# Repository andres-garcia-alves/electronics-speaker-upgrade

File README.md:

# Speaker Upgrade

Speaker modernization (50 watts, 6 ohm) to function as a semi-portable, independent device, separate from the original audio system.

The following features are added:
- Bluetooth audio reception.
- AUX input with a 3.5mm jack for wired connection.
- Slider potentiometer for volume control.
- DC connector for 12V power supply.
- On/off switch button.

&nbsp;

### Notes:

- Power input: 12 VDC
- 2 PCBs are included:
  - Main PCB: for power, BT and audio amplifier features.
  - Auxiliar PCB (for UX): volume slider, LED and AUX audio jack.

&nbsp;

### List of Materials

- 1 x Speaker 10+ watts, 6 ohms
- 1 x Audio Amplifier AN7522N 5W+5W + Heat Sink
- 1 x BT receiver WIN-668 module
- 1 x Lineal Regulator TP7805 + Heat Sink
- 1 x Capacitor 2200uf (electrolitic)
- 1 x Capacitor 1000uf (electrolitic)
- 1 x Capacitor 470uf (electrolitic)
- 1 x Capacitor 10uf (electrolitic)
- 4 x Capacitor 100nf (ceramic)
- 1 x Potentiometer 50K (slider)
- 1 x Resistor 1M ohms
- 1 x Resistor 330K ohms
- 1 x Resistor 47K ohms
- 2 x Resistor 22K ohms
- 2 x Resistor 10K ohms
- 4 x Resistor 3.3K ohms
- 1 x Resistor 680 ohms
- 1 x LED 5mm
- 1 x Audio jack 3.5mm
- 1 x Switch button (audio source)
- 1 x Rocker button (power on/off)
- 1 x DC Jack (power)
- 1 x JST 2-pins connector (or similar)
- 1 x JST 5-pins connector (or similar)
- 1 x JST 6-pins connector (or similar)
- Wires

&nbsp;

### Screenshots

| Breadboard                                           | Assembly                                             |
|------------------------------------------------------|------------------------------------------------------|
|                   |                     |

| Assembly                                             | Assembly                                             |
|------------------------------------------------------|------------------------------------------------------|
|                     |                     |

| Schematics Diagram                                   | PCB Diagram                                          |
|------------------------------------------------------|------------------------------------------------------|
|              |                     |

| PCB Render 3D                                        | PCB Render 3D                                        |
|------------------------------------------------------|------------------------------------------------------|
|               |            |

| Project Final                                        | Project Final                                        |
|------------------------------------------------------|------------------------------------------------------|
|                |                |

See 'Resources' folder for more pictures & videos of the project.

&nbsp;

### Version History

v1.0 (2026.02.15) - Adding base schematics and PCB.  
v1.1 (2026.02.16) - Improvements on schematics and PCB.  
v1.2 (2026.02.17) - Minor improvements on schematics and PCB.  
v1.3 (2026.02.21) - Minor improvements on schematics and PCB.  

&nbsp;

This source code is licensed under GPL v3.0  
Please send me your feedback about this project: andres.garcia.alves@gmail.com

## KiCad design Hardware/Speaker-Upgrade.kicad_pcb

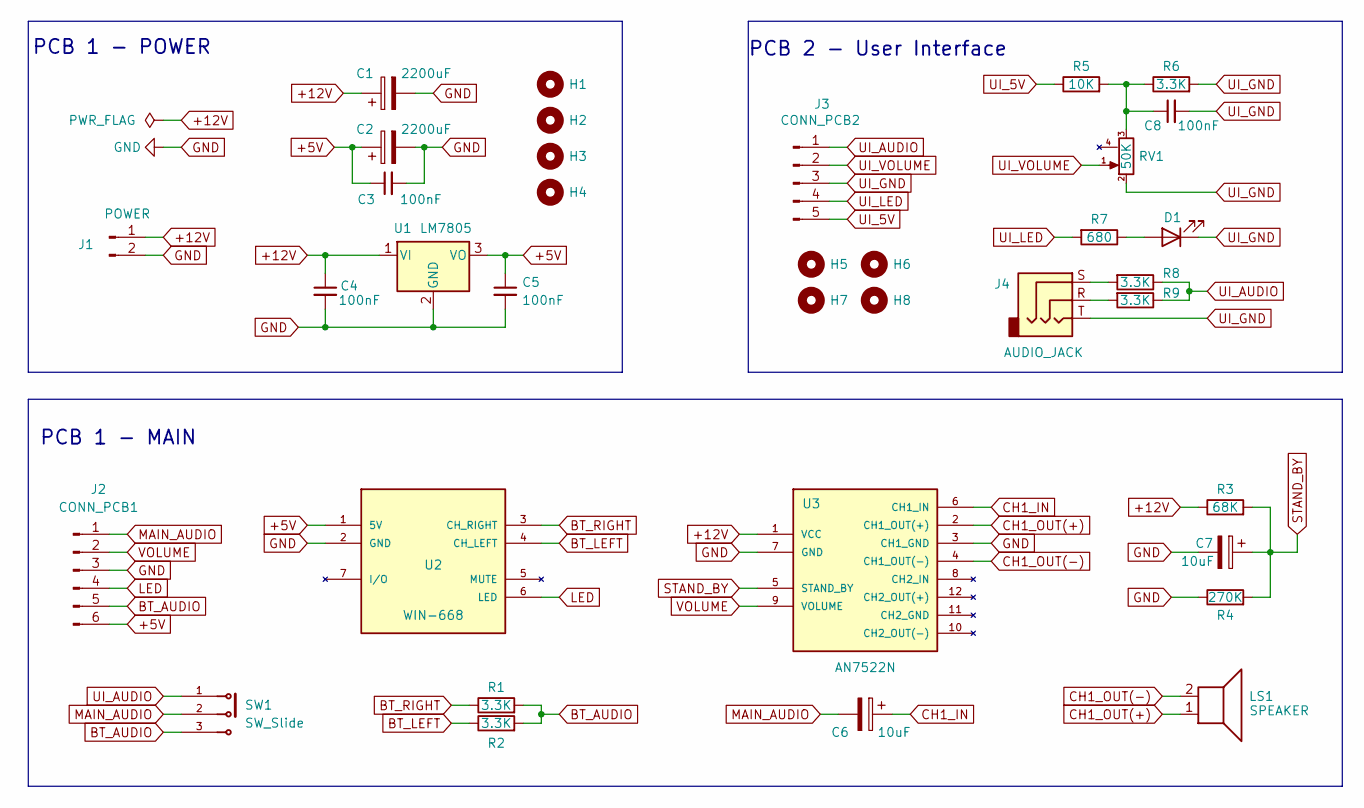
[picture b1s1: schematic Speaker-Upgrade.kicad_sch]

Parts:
C1: 2200uF; C_Radial_D10.0mm_H12.5mm_P5.00mm
C2: 2200uF; C_Radial_D10.0mm_H16.0mm_P5.00mm
C3, C4, C5, C8: 100nF; C_Disc_D6.0mm_W2.5mm_P5.00mm
C6: 10uF; C_Radial_D10.0mm_H16.0mm_P5.00mm
C7: 10uF; C_Radial_D6.3mm_H11.0mm_P2.50mm
D1: LED; LED_D5.0mm
H1, H2, H3, H4, H5, H6, H7, H8: MountingHole; MountingHole_2.2mm_M2
J1: POWER; JST_EH_B2B-EH-A_1x02_P2.50mm_Vertical
J2: CONN_PCB1; PinHeader_2x06_P2.54mm_Vertical
J3: CONN_PCB2; JST_EH_S5B-EH_1x05_P2.50mm_Horizontal
J4: AUDIO_JACK; Jack_3.5mm_Vertical
LS1: SPEAKER; JST_EH_B2B-EH-A_1x02_P2.50mm_Vertical
R1, R2: 3.3K; R_Axial_DIN0207_L6.3mm_D2.5mm_P2.54mm_Vertical
R3: 68K; R_Axial_DIN0207_L6.3mm_D2.5mm_P2.54mm_Vertical
R4: 270K; R_Axial_DIN0207_L6.3mm_D2.5mm_P2.54mm_Vertical
R5: 10K; R_Axial_DIN0207_L6.3mm_D2.5mm_P7.62mm_Horizontal
R6, R8, R9: 3.3K; R_Axial_DIN0207_L6.3mm_D2.5mm_P7.62mm_Horizontal
R7: 680; R_Axial_DIN0207_L6.3mm_D2.5mm_P7.62mm_Horizontal
RV1: 50K; Potentiometer_Custom_Variant_A
SW1: SW_Slide; SW_1825159-1
U1: LM7805; TO-220-3_Vertical
U2: WIN-668; PinSocket_1x07_P2.54mm_Vertical
U3: AN7522N; Audio_Amplifier_AN7522N

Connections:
+5V: C2.1, C3.1, C5.1, J2.6, U1.3 (VO), U2.1 (5V)
+12V: C1.1, C4.1, J1.1, R3.1, U1.1 (VI), U3.1 (VCC)
BT_AUDIO: J2.5, R1.2, R2.2, SW1.3
BT_LEFT: R2.1, U2.4 (CH_LEFT)
BT_RIGHT: R1.1, U2.3 (CH_RIGHT)
CH1_IN: C6.1, U3.6 (CH1_IN)
CH1_OUT(+): LS1.1, U3.2 (CH1_OUT(+))
CH1_OUT(-): LS1.2, U3.4 (CH1_OUT(-))
GND: C1.2, C2.2, C3.2, C4.2, C5.2, C7.2, J1.2, J2.3, R4.1, U1.2 (GND), U2.2 (GND), U3.3 (CH1_GND), U3.7 (GND)
LED: J2.4, U2.6 (LED)
MAIN_AUDIO: C6.2, J2.1, SW1.2
unnamed: C8.1, R5.2, R6.1, RV1.3
unnamed: D1.2 (A), R7.1
unnamed: J4.R, R9.2
unnamed: J4.S, R8.2
STAND_BY: C7.1, R3.2, R4.2, U3.5 (STAND_BY)
UI_5V: J3.5, R5.1
UI_AUDIO: J3.1, R8.1, R9.1, SW1.1
UI_GND: C8.2, D1.1 (K), J3.3, J4.T, R6.2, RV1.2
UI_LED: J3.4, R7.2
UI_VOLUME: J3.2, RV1.1
VOLUME: J2.2, U3.9 (VOLUME)

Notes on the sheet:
PCB 2 - User Interface
PCB 1 - POWER
PCB 1 - MAIN

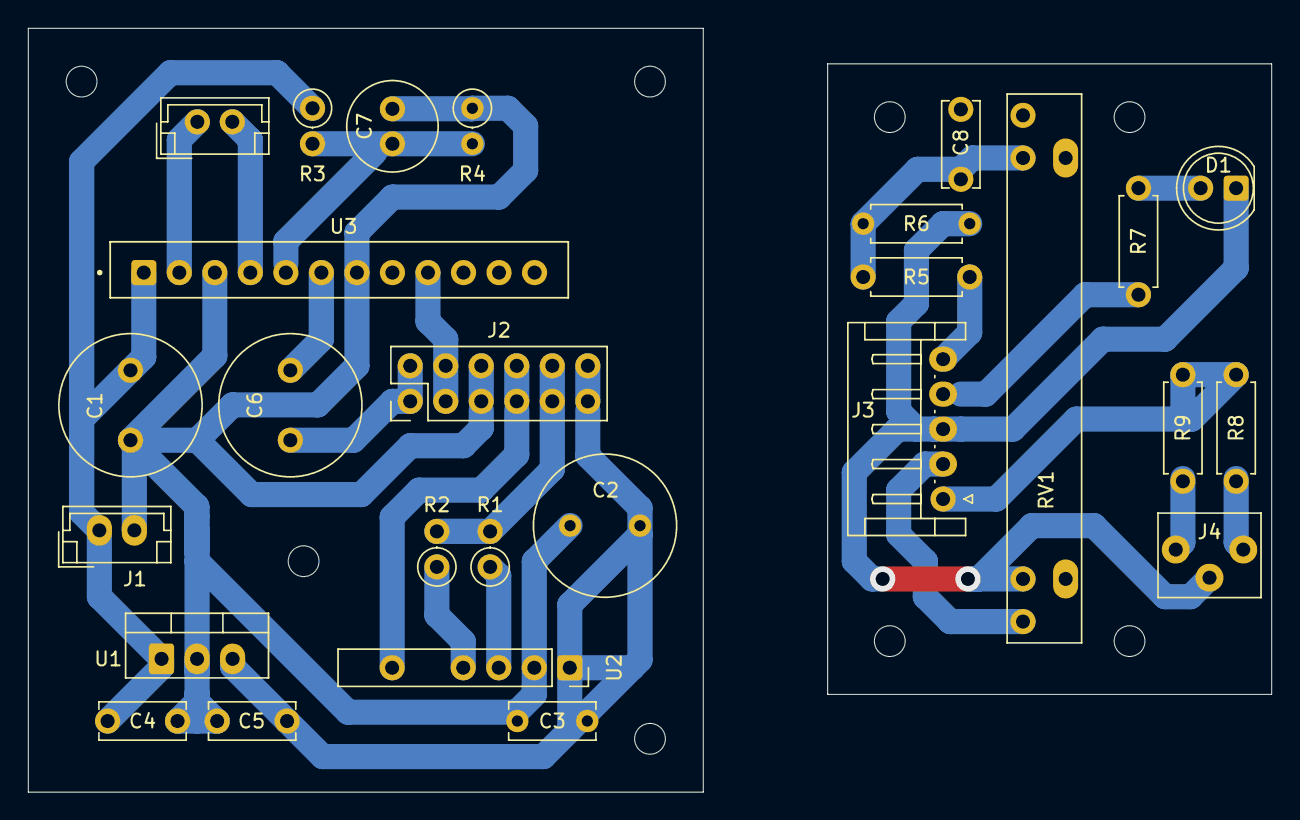
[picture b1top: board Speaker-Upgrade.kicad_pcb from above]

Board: 2 copper layers, 88.9 x 54.6 mm, 35 parts (0 on the bottom side), 22 nets.

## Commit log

2026-02-16 Improvements on schematics and PCB
2026-02-17 Minor improvements on schematics and PCB
2026-02-18 Adding 'Resources' files
2026-03-02 Adding 3D model
2026-03-11 udpate 'Resources' folder
